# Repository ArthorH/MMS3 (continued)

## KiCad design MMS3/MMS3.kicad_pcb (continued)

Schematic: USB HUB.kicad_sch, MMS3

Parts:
C900: 100nF; C_0402; Voltage Rated 50V; Tolerance ±10%; Part CL05B104KB54PNC; LCSC C307331
C902: 10uF; C_0402; Voltage Rated 6.3V; Tolerance ±20%; Part CL05A106MQ5NUNC; LCSC C15525
C904: 1uF; C_0402; Voltage Rated 25V; Tolerance ±10%; Part CL05A105KA5NQNC; LCSC C52923
D301: Red; D_0603; Part KT-0603R; LCSC C2286
R16, R17, R902, R903, R906, R907: 22Ω; R_0402; Overload Voltage (Max) 50V; Tolerance ±1%; Part 0402WGF220JTCE; LCSC C25092
R18, R19, R20, R21: 22Ω; R_0402; Overload Voltage (Max) 50V; Tolerance ±1%; Part 0402WGF220JTCE; LCSC C25092; not fitted
R308: 1kΩ; R_0402; Overload Voltage (Max) 50V; Tolerance ±1%; Part 0402WGF1001TCE; LCSC C11702
U302: CH334P; QFN-16-1EP_3x3mm_P0.5mm_EP1.7x1.7mm
Y900: Crystal_GND24; Crystal_SMD_3225-4Pin_3.2x2.5mm; LCSC C9002

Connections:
+5V: C904.1, D301.2, U302.15 (5V); also elsewhere on the board
/MCU/USB_MCU.D+: R21.2, R907.1; also elsewhere on the board
/MCU/USB_MCU.D-: R20.2, R906.1; also elsewhere on the board
/STlink-BMprobe/ST-LINK.D+: R903.1; also elsewhere on the board
/STlink-BMprobe/ST-LINK.D-: R902.1; also elsewhere on the board
/USB HUB/USBBYP.D+: R18.1, R21.1
/USB HUB/USBBYP.D-: R19.1, R20.1
/USB HUB/USBIN1.D+: R16.2, R18.2; also elsewhere on the board
/USB HUB/USBIN1.D-: R17.2, R19.2; also elsewhere on the board
/USB HUB/USBIN1_R.D+: R16.1, U302.12 (DPU)
/USB HUB/USBIN1_R.D-: R17.1, U302.11 (DMU)
/USB HUB/USBOUT1_R.D+: R903.2, U302.6 (DP3)
/USB HUB/USBOUT1_R.D-: R902.2, U302.5 (DM3)
/USB HUB/USBOUT2_R.D+: R907.2, U302.8 (DP2)
/USB HUB/USBOUT2_R.D-: R906.2, U302.7 (DM2)
GND: C900.2, C902.2, C904.2, U302.17 (GND), Y900.2, Y900.4; also elsewhere on the board
unnamed: D301.1, R308.2
unnamed: C900.1, C902.1, U302.16 (3V3)
unnamed: R308.1, U302.14 (PGANG)
unnamed: U302.2 (XI), Y900.3
unnamed: U302.1 (XO), Y900.1

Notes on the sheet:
NOTICE:
BM-probe bypass
Hipity hopity SI is now my property :)
USB HUB TO MCU AND STLINK
USB HUB BYPASS
STM32 direct link

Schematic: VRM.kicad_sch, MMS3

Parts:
C30, C31, C32, C33, C34, C35: 10uF; C_0805; Voltage Rated 50V; Tolerance ±10%; Part GRM21BR61H106KE43L; LCSC C440198
C38, C39: 220nF; C_0805; Voltage Rated 50V; Tolerance ±10%; Part CL21B224KBFNNNE; LCSC C5378
C40: 100nF; C_0805; Voltage Rated 100V; Tolerance ±10%; Part CL21B104KCFNNNE; LCSC C28233
C41, C42, C45, C46, C47: 22uF; C_0805; Voltage Rated 25V; Tolerance ±20%; Part CL21A226MAQNNNE; LCSC C45783
C43: 47pF; C_0402; Voltage Rated 50V; Tolerance ±5%; Part 0402CG470J500NT; LCSC C1567
C44: 4.7nF; C_0402; Voltage Rated 50V; Tolerance ±10%; Part 0402B472K500NT; LCSC C1538
C49, C50: 100uF; CP_Elec_10x10; MPN VZH101M1KTR-1010; LCSC C249838
C69, C74: 100nF; C_0402; Voltage Rated 16V; Tolerance ±10%; Part CL05B104KO5NNNC; LCSC C1525
D1: SMF58CA; D_SOD-123FL; Clamping Voltage 93.6V; Voltage - Breakdown 71.2V; Part SMF58CA; LCSC C42371753
D3, D4: SS510B; D_SMB; Forward Voltage (Vf@If) 0.85V@5.0A; Reverse Voltage (Vr) 100V; Part SS510B; LCSC C7420368
L1: YSPI1050-100M; L_Sunlord_MWSA1005S; LCSC C497897
R33, R34: 24.9kΩ; R_0402; Overload Voltage (Max) 50V; Tolerance ±1%; Part 0402WGF2402TCE; LCSC C25874
R36: 43kΩ; R_0603; Overload Voltage (Max) 75V; Tolerance ±1%; Part 0603WAF4302T5E; LCSC C23172
R37: 8.2kΩ; R_0402; Overload Voltage (Max) 50V; Tolerance ±1%; Part 0402WGF8201TCE; LCSC C25924
R38: 12kΩ; R_0402; Overload Voltage (Max) 50V; Tolerance ±1%; Part 0402WGF1202TCE; LCSC C25752
R39: 240kΩ; R_0603; Overload Voltage (Max) 75V; Tolerance ±1%; Part 0603WAF2403T5E; LCSC C4197
TP16, TP17, TP18, TP19, TP20: TestPoint; TestPoint_Pad_D1.0mm
U2: TPS54560BDDA; Texas_R-PDSO-G8_EP2.95x4.9mm_Mask2.4x3.1mm_ThermalVias
U15: AMS1117-3.3; SOT-223-3_TabPin2

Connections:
+3V3: C69.1, U15.2 (VO); also elsewhere on the board
+5V: C50.1, C74.1, D4.1, U15.3 (VI); also elsewhere on the board
/VRM/Cap_protec: C30.2, C31.1, C32.2, C33.1, C34.2, C35.1, C38.2, C39.1, R33.2, R34.1
BRD_VIN: C30.1, C32.1, C34.1, C38.1, C49.1, D1.1, R33.1, TP16.1 (1_1), U2.2 (VIN), U2.3 (EN); also elsewhere on the board
GND: C31.2, C33.2, C35.2, C39.2, C41.2, C42.2, C43.2, C44.2, C45.2, C46.2, C47.2, C49.2, C50.2, C69.2, C74.2, D1.2, D3.2, R34.2, R37.2, R39.2, U2.7 (GND), U2.9 (GND), U15.1 (GND); also elsewhere on the board
unnamed: C41.1, C42.1, C45.1, C46.1, C47.1, D4.2, L1.2, R36.1, TP19.1 (1_1)
unnamed: C44.1, R38.2
unnamed: C40.2, U2.1 (BOOT)
unnamed: C43.1, R38.1, TP17.1 (1_1), U2.6 (COMP)
unnamed: R36.2, R37.1, TP18.1 (1_1), U2.5 (FB)
unnamed: R39.1, TP20.1 (1_1), U2.4 (RT/CLK)
unnamed: C40.1, D3.1, L1.1, U2.8 (SW)

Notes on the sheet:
saved for kebab on that one alone
INFORMATION
KEEP CRIPPAGE DISTANCE 1.26MM MIN!
Thats not sketch ... thats BOM-bastic!
RANDOM NUMBER GENERATOR OUTPUT
60V MAX
IEC 60664-1 Material Group III (CTI < 400; typical FR-4 = IIIa): 1.25 mm

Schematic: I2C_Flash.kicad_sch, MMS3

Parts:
C27: 100nF; C_0402; Voltage Rated 50V; Tolerance ±10%; Part CL05B104KB54PNC; LCSC C307331
R23, R24, R25: 10kΩ; R_0402; Overload Voltage (Max) 50V; Tolerance ±1%; Part 0402WGF1002TCE; LCSC C25744; not fitted
R26, R28, R29, R30: 10kΩ; R_0402; Overload Voltage (Max) 50V; Tolerance ±1%; Part 0402WGF1002TCE; LCSC C25744
U6: AT24C256C; SOIC-8_5.3x5.3mm_P1.27mm; Supply Voltage 1.7V~5.5V; Part AT24C256C-SSHL-T; LCSC C6482

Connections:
+3V3: C27.1, R28.1, R29.1, R30.1, U6.8 (VCC); also elsewhere on the board
/I2C_Flash/A0: R23.1, R28.2, U6.1 (A0)
/I2C_Flash/A1: R24.1, R29.2, U6.2 (A1)
/I2C_Flash/A2: R25.1, R30.2, U6.3 (A2)
/I2C_Flash/I2C_Memory.SCL: U6.6 (SCL); also elsewhere on the board
/I2C_Flash/I2C_Memory.SDA: U6.5 (SDA); also elsewhere on the board
GND: C27.2, R23.2, R24.2, R25.2, R26.2, U6.4 (GND); also elsewhere on the board
unnamed: R26.1, U6.7 (WP)

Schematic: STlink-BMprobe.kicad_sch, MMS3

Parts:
C28, C29: 33pF; C_0402; Voltage Rated 50V; Tolerance ±5%; Part 0402CG330J500NT; LCSC C1562
C700: 1uF; C_0402; Voltage Rated 25V; Tolerance ±10%; Part CL05A105KA5NQNC; LCSC C52923
C701, C702, C703, C704, C705, C706: 100nF; C_0402; Voltage Rated 50V; Tolerance ±10%; Part CL05B104KB54PNC; LCSC C307331
D700, D701: Red; D_0603; Part KT-0603R; LCSC C2286
J3: Programming header; PinHeader_1x06_P1.27mm_Vertical; not fitted
Q700: MMST3904; SOT-23; Part MMST3904; LCSC C20526
R700, R702: 100kΩ; R_0402; Overload Voltage (Max) 50V; Tolerance ±1%; Part 0402WGF1003TCE; LCSC C25741
R701, R703, R705, R709: 10kΩ; R_0402; Overload Voltage (Max) 50V; Tolerance ±1%; Part 0402WGF1002TCE; LCSC C25744
R704, R708, R715, R716: 22Ω; R_0402; Overload Voltage (Max) 50V; Tolerance ±1%; Part 0402WGF220JTCE; LCSC C25092
R706: 10kΩ; R_0402; Overload Voltage (Max) 50V; Tolerance ±1%; Part 0402WGF1002TCE; LCSC C25744; not fitted
R707, R713: 220Ω; R_0402; Overload Voltage (Max) 50V; Tolerance ±1%; Part 0402WGF2200TCE; LCSC C25091
R710, R714: 100Ω; R_0402; Overload Voltage (Max) 50V; Tolerance ±1%; Part 0402WGF1000TCE; LCSC C25076
R711: 24.9kΩ; R_0402; Overload Voltage (Max) 50V; Tolerance ±1%; Part 0402WGF2402TCE; LCSC C25874
R712: 1.5kΩ; R_0402; Overload Voltage (Max) 50V; Tolerance ±1%; Part 0402WGF1501TCE; LCSC C25867
TP9, TP10, TP11, TP12, TP13, TP14: TestPoint; TestPoint_Pad_D1.0mm
U700: STM32F103CBTx; LQFP-48_7x7mm_P0.5mm; LCSC C8304
Y700: Crystal_GND24; CRYSTAL-SMD_4P-L3.2-W2.5-BL; MPN 3225-8.00-20-10-10/4B; LCSC C7424755

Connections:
+3V3: C700.1, C701.1, C702.1, C703.1, C704.1, C705.1, J3.1, Q700.3 (C), R700.1, R701.1, R707.1, U700.1 (VBAT), U700.9 (VDDA), U700.24 (VDD), U700.36 (VDD), U700.48 (VDD); also elsewhere on the board
+5V: R709.1; also elsewhere on the board
/MCU/SWD.SWCLK: R704.2, R715.1, TP10.1 (1_1); also elsewhere on the board
/MCU/SWD.SWDIO: R716.1, TP9.1 (1_1); also elsewhere on the board
/MCU/SWD.~RST: R708.1, TP11.1 (1_1); also elsewhere on the board
/STlink-BMprobe/CLK: J3.3, U700.37 (PA14)
/STlink-BMprobe/DIO: J3.2, U700.34 (PA13)
/STlink-BMprobe/LED: D700.1, D701.2, U700.30 (PA9)
/STlink-BMprobe/ST-LINK.D+: R712.2, TP13.1 (1_1), U700.33 (PA12); also elsewhere on the board
/STlink-BMprobe/ST-LINK.D-: TP12.1 (1_1), U700.32 (PA11); also elsewhere on the board
/STlink-BMprobe/STLINK-BOOT0: J3.6, R702.2, U700.44 (BOOT0)
/STlink-BMprobe/STLINK-OSC_IN: C28.1, U700.5 (PD0), Y700.1
/STlink-BMprobe/STLINK-OSC_OUT: C29.1, U700.6 (PD1), Y700.3
/STlink-BMprobe/STLINK-RST: C706.1, J3.4, R700.2, U700.7 (NRST)
/STlink-BMprobe/STLINK.RX: U700.12 (PA2)
/STlink-BMprobe/STLINK.TX: U700.13 (PA3)
/STlink-BMprobe/SWO: U700.31 (PA10)
/STlink-BMprobe/USB_RENUM: R710.2, TP14.1 (1_1), U700.38 (PA15)
GND: C28.2, C29.2, C700.2, C701.2, C702.2, C703.2, C704.2, C705.2, C706.2, J3.5, R702.1, R703.2, R705.1, R706.1, R711.2, R713.2, U700.8 (VSSA), U700.23 (VSS), U700.35 (VSS), U700.47 (VSS), Y700.2, Y700.4; also elsewhere on the board
unnamed: D700.2, R707.2
unnamed: D701.1, R713.1
unnamed: Q700.1 (B), R709.2, R710.1, R711.1
unnamed: Q700.2 (E), R712.1
unnamed: R701.2, R703.1, U700.10 (PA0)
unnamed: R704.1, U700.15 (PA5)
unnamed: R708.2, U700.18 (PB0)
unnamed: R714.2, U700.25 (PB12)
unnamed: R715.2, U700.26 (PB13)
unnamed: R714.1, R716.2, U700.27 (PB14)
unnamed: R705.2, U700.2 (PC13)
unnamed: R706.2, U700.3 (PC14)

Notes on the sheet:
MANDATORY CB VERSION
Monitor voltage rail 3V3 instead of target MCU voltage
Should be 1k5, but we try 1k2 because it is in basic parts
NOTICE:
Alternative GD32F103CB
https://stm32world.com/wiki/DIY_STM32_Programmer_(ST-Link/V2-1)
Credit to:
CAUTION:
UART FLIP HERE
https://github.com/lbthomsen/st-link/tree/master
C707=C708 = (CL - 4pF) * 2
ALTERNATE PART: GigaDevice Semicon Beijing GD32F103CBT6 PIN AND FW COMPATIBLE WAZZUP BEIJING
ACTIVITY LED
SWD
for providing amazing reverse engeenering of ST-link
NOTE:
FORCE RENUMERATION OF USB DEVICES
Populate with STM32F103C8, STM32F103CB

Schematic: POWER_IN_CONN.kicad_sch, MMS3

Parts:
J2: AMASS XT60; AMASS_XT60PW-M_1x02_P7.20mm_Horizontal; LCSC C98732

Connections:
BRD_VIN: J2.2; also elsewhere on the board
GND: J2.1; also elsewhere on the board

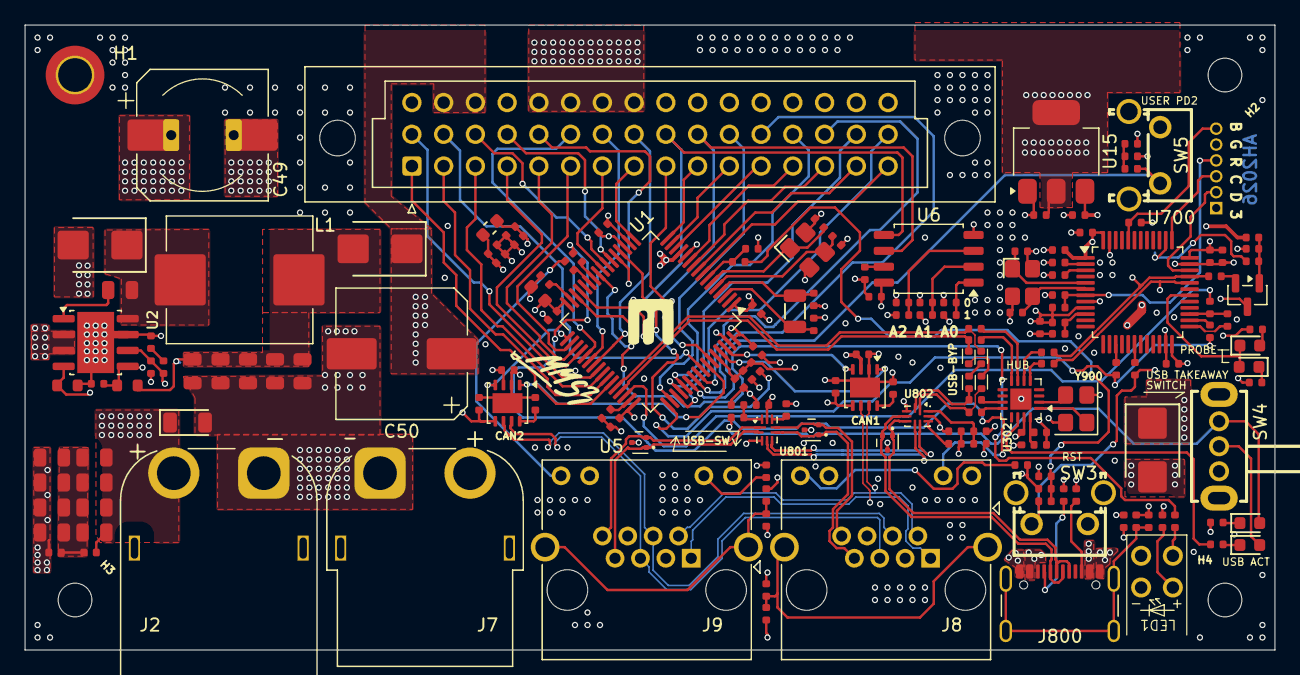
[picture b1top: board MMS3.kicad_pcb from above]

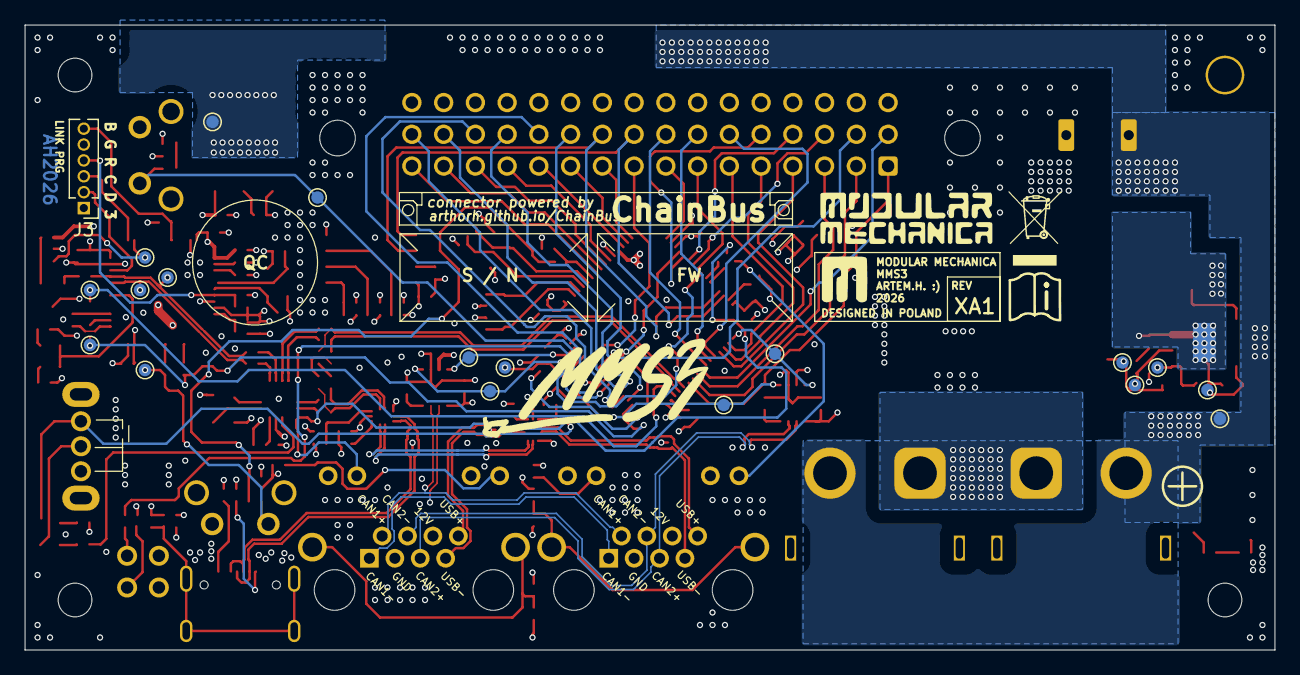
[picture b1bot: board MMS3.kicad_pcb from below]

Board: 4 copper layers, 100.0 x 50.0 mm, 192 parts (19 on the bottom side), 143 nets.

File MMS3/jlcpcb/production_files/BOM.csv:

"Id" "Designator" "Footprint" "Quantity" "Designation" "LCSC" 
1 "C1, C2, C7" "C_0402" 3 "10nF"   
2 "C3, C4, C5, C6, C12, C13, C15, C19, C20, C21, C22, C23, C25, C26, C27, C69, C74, C312, C313, C701, C702, C703, C704, C705, C706, C800, C900" "C_0402" 27 "100nF"   
3 "C8, C9" "C_0402" 2 "18pF"   
4 "C10, C11" "C_0402" 2 "22pF"   
5 "C16, C17" "C_0402" 2 "2.2uF"   
6 "C24" "C_0603" 1 "10uF"   
7 "C28, C29" "C_0402" 2 "33pF"   
8 "C30, C31, C32, C33, C34, C35" "C_0805" 6 "10uF"   
9 "C36, C37, C902" "C_0402" 3 "10uF"   
10 "C38, C39" "C_0805" 2 "220nF"   
11 "C40" "C_0805" 1 "100nF"   
12 "C41, C42, C45, C46, C47" "C_0805" 5 "22uF"   
13 "C43" "C_0402" 1 "47pF"   
14 "C44" "C_0402" 1 "4.7nF"   
15 "C49, C50" "CP_Elec_10x10" 2 "100uF"   
16 "C700, C904" "C_0402" 2 "1uF"   
17 "D1" "D_SOD-123FL" 1 "SMF58CA"   
18 "D3, D4, D5" "D_SMB" 3 "SS510B"   
19 "D6, D301, D700, D701" "D_0603" 4 "Red"   
20 "FB401" "FB_0603" 1 "~"   
21 "J1" "DIN41612_C2_3x16_Female_Vertical_THT" 1 "86093488324755V1LF"   
22 "J2" "AMASS_XT60PW-M_1x02_P7.20mm_Horizontal" 1 "AMASS XT60"   
23 "J7" "AMASS_XT60PW-F_1x02_P7.20mm_Horizontal" 1 "AMASS XT60"   
24 "J800" "USB_C_Receptacle_GCT_USB4105-xx-A_16P_TopMnt_Horizontal" 1 "USB_C_Receptacle_USB2.0_16P"   
25 "L1" "L_Sunlord_MWSA1005S" 1 "YSPI1050-100M"   
26 "Q700" "SOT-23" 1 "MMST3904"   
27 "R1, R2, R3, R4, R707, R713" "R_0402" 6 "220Ω"   
28 "R5, R6, R7" "R_0402" 3 "33kΩ"   
29 "R8, R9" "R_0402" 2 "5.1kΩ"   
30 "R10, R14, R15, R26, R28, R29, R30, R500, R501, R701, R703, R705, R709, R802, R804, R805, R807" "R_0402" 17 "10kΩ"   
31 "R12, R13, R22, R710, R714" "R_0402" 5 "100Ω"   
32 "R16, R17, R704, R708, R715, R716, R902, R903, R906, R907" "R_0402" 10 "22Ω"   
33 "R27, R31, R40, R308" "R_0402" 4 "1kΩ"   
34 "R33, R34, R711" "R_0402" 3 "24.9kΩ"   
35 "R36" "R_0603" 1 "43kΩ"   
36 "R37" "R_0402" 1 "8.2kΩ"   
37 "R38" "R_0402" 1 "12kΩ"   
38 "R39" "R_0603" 1 "240kΩ"   
39 "R700, R702" "R_0402" 2 "100kΩ"   
40 "R712" "R_0402" 1 "1.5kΩ"   
41 "R803, R806" "R_0402" 2 "22kΩ"   
42 "SW3, SW5" "SW-TH_4P-L7.3-TC-6615Z-12.5-260" 2 "TC-6615Z-12.5-260"   
43 "SW4" "SW-TH_SK12D07VG5-1" 1 "SK12D07VG5"   
44 "U1" "LQFP-64_10x10mm_P0.5mm" 1 "STM32F405RGTx"   
45 "U2" "Texas_R-PDSO-G8_EP2.95x4.9mm_Mask2.4x3.1mm_ThermalVias" 1 "TPS54560BDDA"   
46 "U4, U5, U401" "SOT-723" 3 "TPD2EUSB30DRTR-TP"   
47 "U6" "SOIC-8_5.3x5.3mm_P1.27mm" 1 "AT24C256C"   
48 "U15" "SOT-223-3_TabPin2" 1 "AMS1117-3.3"   
49 "U302" "QFN-16-1EP_3x3mm_P0.5mm_EP1.7x1.7mm" 1 "CH334P"   
50 "U500, U501" "HVSON-8-1EP_3x3mm_P0.65mm_EP1.6x2.4mm" 2 "TJA1044GTK_3Z"   
51 "U700" "LQFP-48_7x7mm_P0.5mm" 1 "STM32F103CBTx"   
52 "U801, U802" "UQFN-10_1.4x1.8mm_P0.4mm" 2 "FSUSB42UMX"   
53 "X1" "OSC-SMD_4P-L3.2-W2.5-BL" 1 "X32258MOB4SI"   
54 "X2" "FC-135R_L3.2-W1.5" 1 "Q13FC1350000400"   
55 "Y700" "CRYSTAL-SMD_4P-L3.2-W2.5-BL" 1 "Crystal_GND24"   
56 "Y900" "Crystal_SMD_3225-4Pin_3.2x2.5mm" 1 "Crystal_GND24"

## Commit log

2026-04-04 initial schematic + front panel
2026-04-08 schematic + partly layout
2026-04-11 almost done
2026-04-13 prod ready
2026-04-13 remove backups
2026-04-21 prod
